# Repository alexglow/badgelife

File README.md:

# badgelife
SAOs... and more?

See my Shitty Add-On tutorial on [Hackster.io](https://www.hackster.io/glowascii/design-a-sh-tty-add-on-in-kicad-06350f)! (Uses KiCad + Bantam desktop PCB mill)

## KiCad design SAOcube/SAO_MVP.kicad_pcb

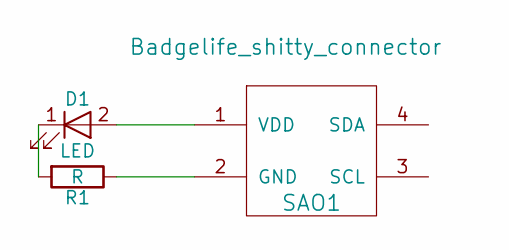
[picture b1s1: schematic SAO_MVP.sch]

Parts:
D1: LED; LED_D5.0mm
R1: R; R_Axial_DIN0207_L6.3mm_D2.5mm_P7.62mm_Horizontal
SAO1: Badgelife_shitty_connector; Badgelife-Shitty-2x2-Edge

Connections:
unnamed: D1.1 (K), R1.2
unnamed: D1.2 (A), SAO1.1 (VDD)
unnamed: R1.1, SAO1.2 (GND)

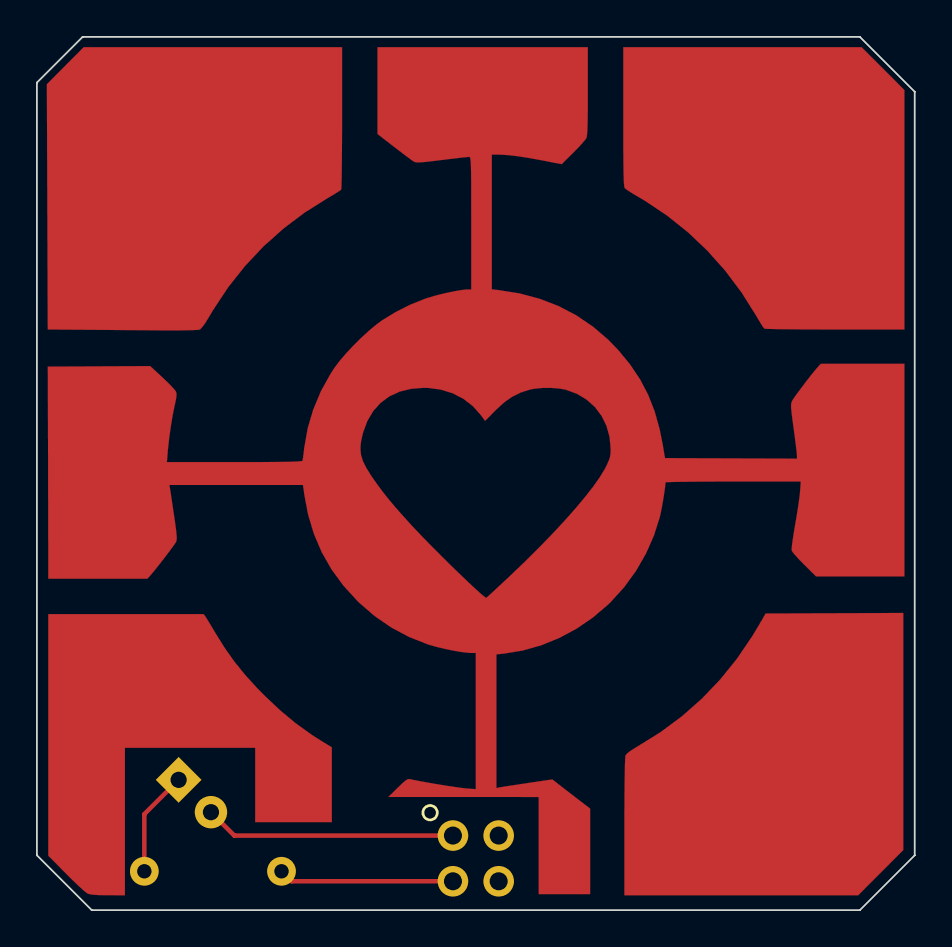
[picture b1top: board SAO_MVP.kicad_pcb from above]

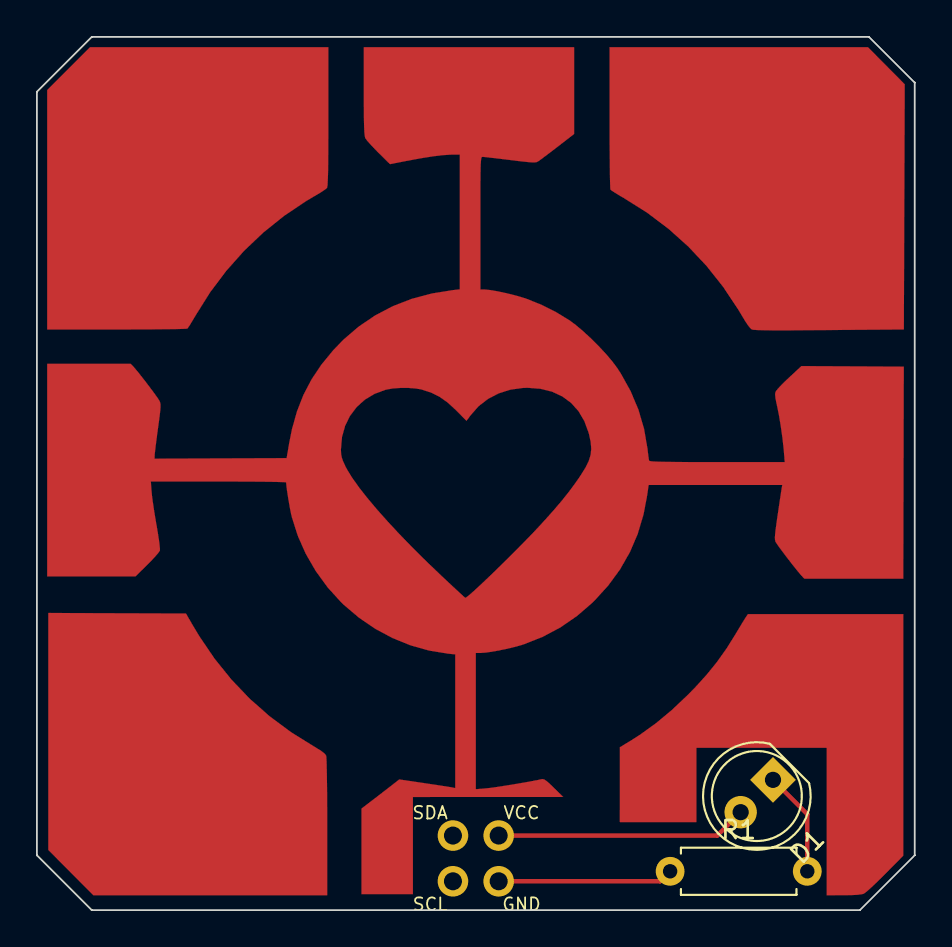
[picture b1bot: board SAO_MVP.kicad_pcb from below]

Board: 2 copper layers, 48.8 x 48.5 mm, 3 parts (2 on the bottom side), 3 nets.

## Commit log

2018-10-29 cube SAO with gerbers for Bantam desktop PCB mill
